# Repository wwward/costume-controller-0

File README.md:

costume-controller-0
====================

Private WIP for ballet costume controller

Using EAGLE 6.5 in "Freemium" mode, FWIW -- wwward

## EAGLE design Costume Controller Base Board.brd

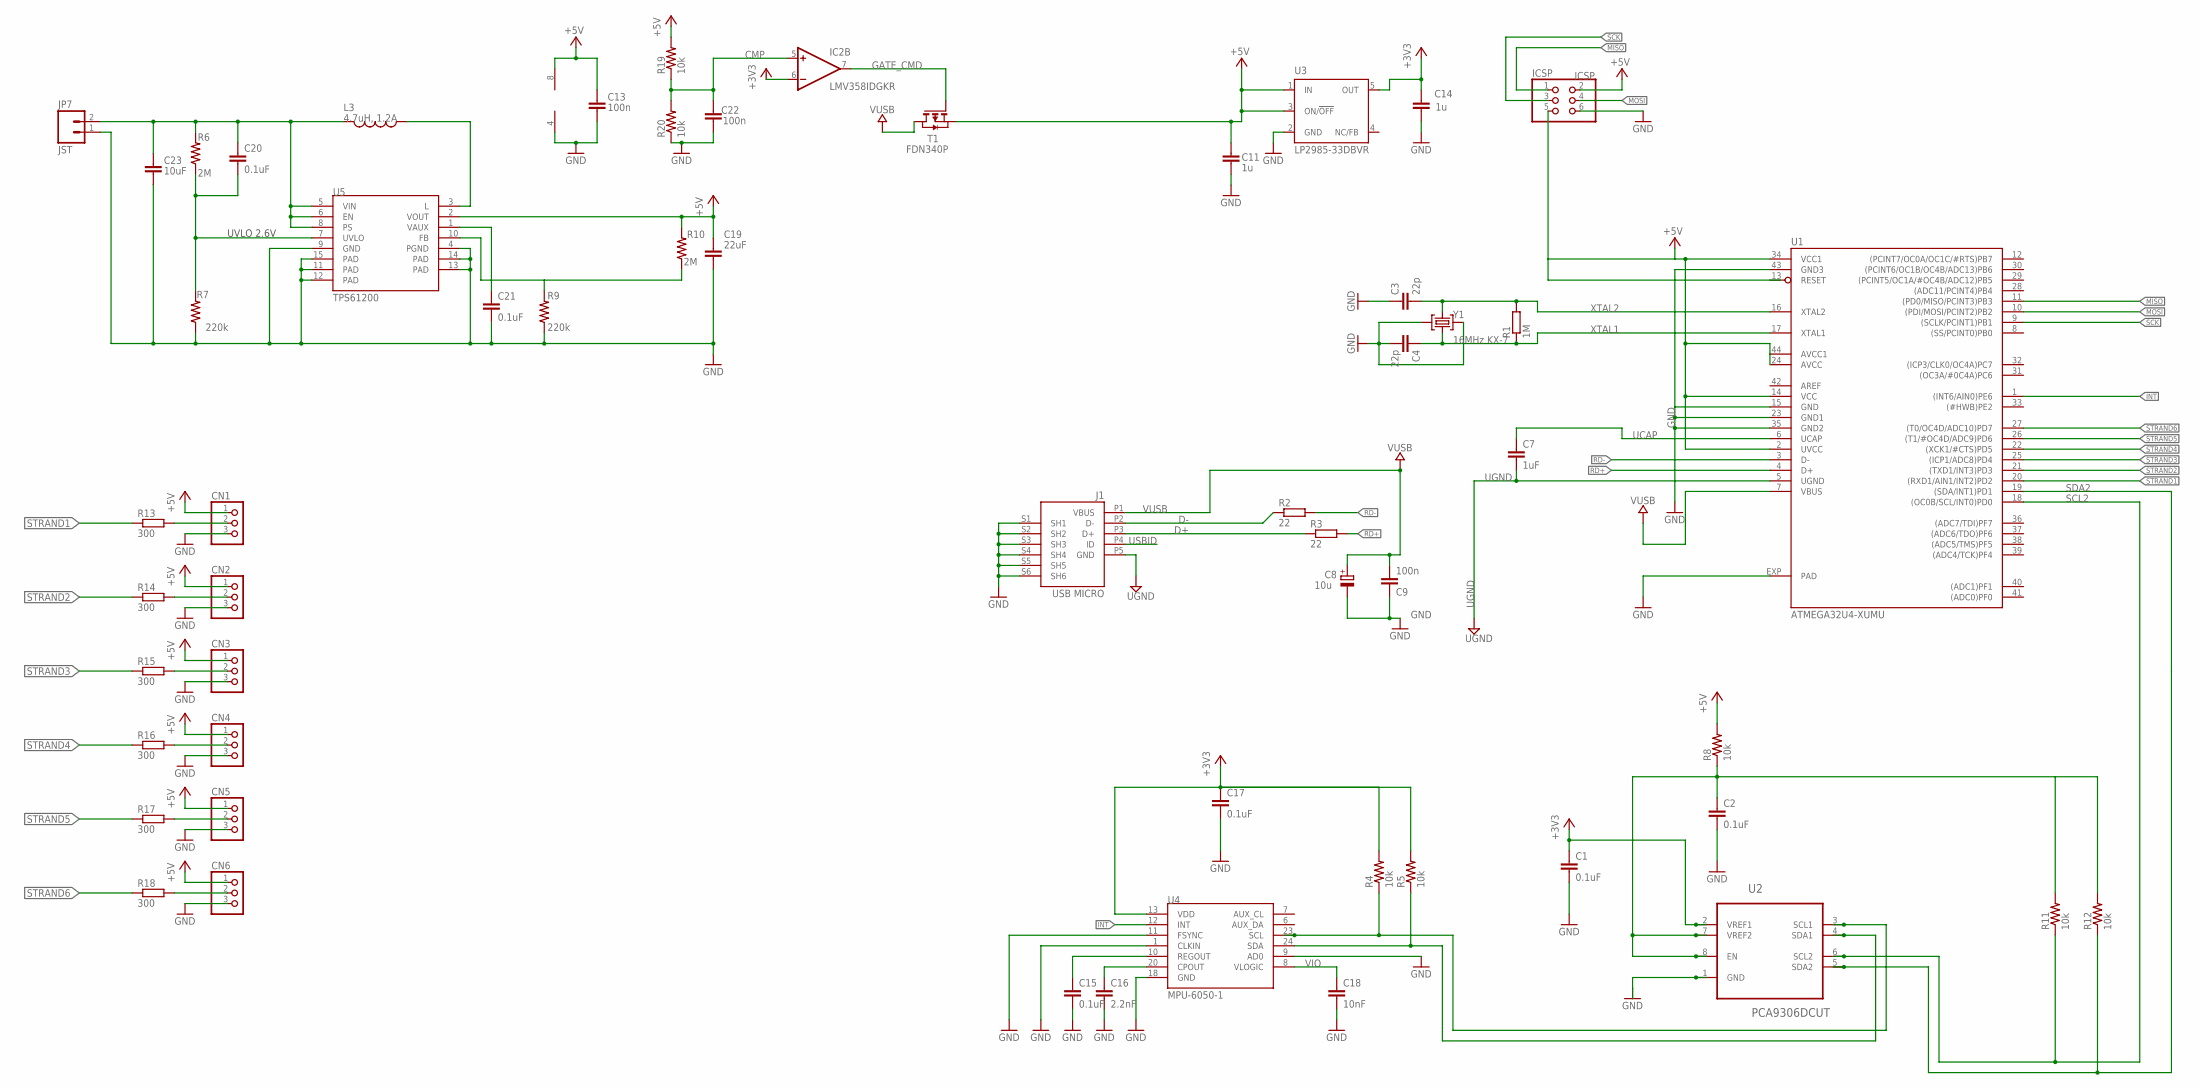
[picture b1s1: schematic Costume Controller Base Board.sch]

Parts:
C1, C2, C15, C17, C20, C21: 0.1uF; 0603-CAP
C3, C4: 22p; C0603-ROUND
C7: 1uF; C0603-ROUND
C8: 10u; SMC_B
C9, C13, C22: 100n; C0603-ROUND
C11, C14: 1u; C0603-ROUND
C16: 2.2nF; 0603-CAP
C18: 10nF; 0603-CAP
C19: 22uF; C0603
C23: 10uF; 1206
CN1, CN2, CN3, CN4, CN5, CN6: JST_3PIN; JSTPH3
IC2: LMV358IDGKR; MSOP08
ICSP: ICSP; 2X03
J1: USB MICRO; CON2_USB_MICRO_B_AT
JP7: JST; JST-2-SMD
L3: 4.7uH, 1.2A; CDRH2D09
R1: 1M; R0603
R2, R3: 22; R0603
R4, R5, R8, R11, R12, R19, R20: 10k; 0603-RES
R6, R10: 2M; 0603-RES
R7, R9: 220k; 0603-RES
R13, R14, R15, R16, R17, R18: 300; R0603
T1: FDN340P; SOT-23
U1: ATMEGA32U4-XUMU; QFN44ML7X7
U2: PCA9306DCUT; SOP50P310X90-8N
U3: LP2985-33DBVR; SOT23-DBV
U4: MPU-6050-1; QFN-24-4MM2
U5: TPS61200; QFN-10_PAD
Y1: 16MHz KX-7; CRYSTAL-3.2-2.5

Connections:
+3V3: C1.1, C14.2, C17.1, IC2.6 (-IN), R4.2, R5.2, U2.2 (VREF1), U3.5 (OUT), U4.13 (VDD)
+5V: C11.2, C13.1, C19.1, CN1.1, CN2.1, CN3.1, CN4.1, CN5.1, CN6.1, IC2.8 (V+), ICSP.2, ICSP.5, R8.2, R10.2, R19.2, T1.2 (S), U1.2 (UVCC), U1.14 (VCC), U1.24 (AVCC), U1.34 (VCC1), U1.44 (AVCC1), U3.1 (IN), U3.3 (ON/!OFF), U5.2 (VOUT)
AREF: U1.42 (AREF)
CMP: C22.2, IC2.5 (+IN), R19.1, R20.2
D+: J1.P3 (D+), R3.1
D-: J1.P2 (D-), R2.1
FB: R9.2, R10.1, U5.10 (FB)
GATE_CMD: IC2.7 (OUT), T1.3 (G)
GND: C1.2, C2.2, C3.1, C4.2, C8.-, C9.1, C11.1, C13.2, C14.1, C15.2, C16.2, C17.2, C18.2, C19.2, C21.2, C22.1, C23.2, CN1.3, CN2.3, CN3.3, CN4.3, CN5.3, CN6.3, IC2.4 (V-), ICSP.6, J1.S1 (SH1), J1.S2 (SH2), J1.S3 (SH3), J1.S4 (SH4), J1.S5 (SH5), J1.S6 (SH6), JP7.1, R7.1, R9.1, R20.1, U1.15 (GND), U1.23 (GND1), U1.35 (GND2), U1.43 (GND3), U1.EXP (PAD), U2.1 (GND), U3.2 (GND), U4.1 (CLKIN), U4.9 (AD0), U4.11 (FSYNC), U4.18 (GND), U5.4 (PGND), U5.9 (GND), U5.11 (PAD), U5.12 (PAD), U5.13 (PAD), U5.14 (PAD), U5.15 (PAD), Y1.2 (GND), Y1.4 (GND)
INT: U1.1 ((INT6/AIN0)PE6), U4.12 (INT)
MISO: ICSP.1, U1.11 ((PD0/MISO/PCINT3)PB3)
MOSI: ICSP.4, U1.10 ((PDI/MOSI/PCINT2)PB2)
unnamed: C16.1, U4.20 (CPOUT)
unnamed: C2.1, R8.1, R11.2, R12.2, U2.7 (VREF2), U2.8 (EN)
unnamed: CN6.2, R18.2
unnamed: L3.P$1 (1), U5.3 (L)
unnamed: C15.1, U4.10 (REGOUT)
unnamed: CN5.2, R17.2
unnamed: CN4.2, R16.2
unnamed: CN3.2, R15.2
unnamed: C21.1, U5.1 (VAUX)
unnamed: CN2.2, R14.2
unnamed: CN1.2, R13.2
RD+: R3.2, U1.4 (D+)
RD-: R2.2, U1.3 (D-)
SCK: ICSP.3, U1.9 ((SCLK/PCINT1)PB1)
SCL1: R4.1, U2.3 (SCL1), U4.23 (SCL)
SCL2: R11.1, U1.18 ((OC0B/SCL/INT0)PD0), U2.6 (SCL2)
SDA1: R5.1, U2.4 (SDA1), U4.24 (SDA)
SDA2: R12.1, U1.19 ((SDA/INT1)PD1), U2.5 (SDA2)
STRAND1: R13.1, U1.20 ((RXD1/AIN1/INT2)PD2)
STRAND2: R14.1, U1.21 ((TXD1/INT3)PD3)
STRAND3: R15.1, U1.25 ((ICP1/ADC8)PD4)
STRAND4: R16.1, U1.22 ((XCK1/#CTS)PD5)
STRAND5: R17.1, U1.26 ((T1/#OC4D/ADC9)PD6)
STRAND6: R18.1, U1.27 ((T0/OC4D/ADC10)PD7)
UCAP: C7.1, U1.6 (UCAP)
UGND: C7.2, J1.P5 (GND), U1.5 (UGND)
USBID: J1.P4 (ID)
UVLO: C20.2, R6.1, R7.2, U5.7 (UVLO)
VIN: C20.1, C23.1, JP7.2, L3.P$2 (2), R6.2, U5.5 (VIN), U5.6 (EN), U5.8 (PS)
VIO: C18.1, U4.8 (VLOGIC)
VUSB: C8.+, C9.2, J1.P1 (VBUS), T1.1 (D), U1.7 (VBUS)
XTAL1: C4.1, R1.1, U1.17 (XTAL1), Y1.1 (C1)
XTAL2: C3.2, R1.2, U1.16 (XTAL2), Y1.3 (C2)

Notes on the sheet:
UVLO 2.6V

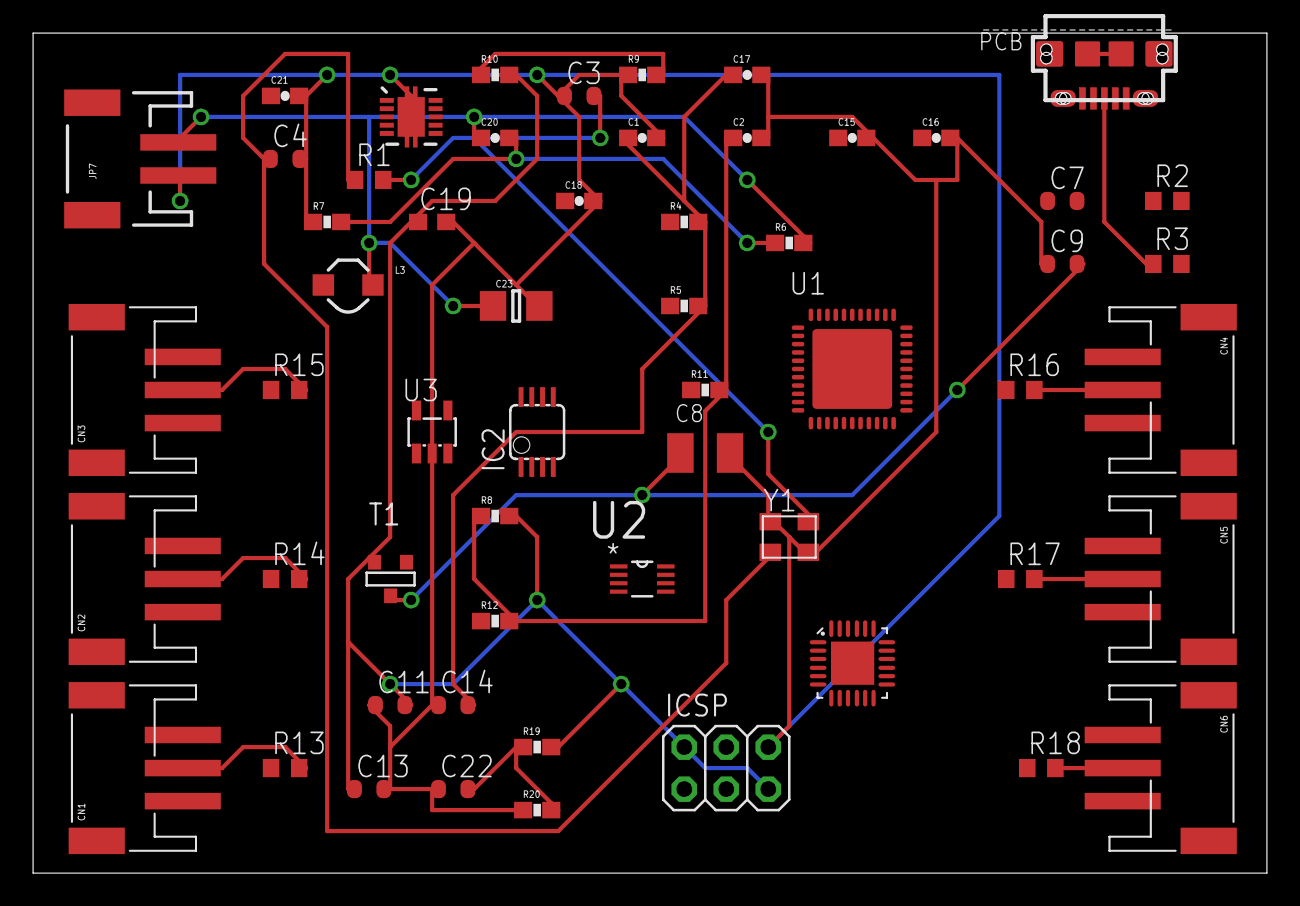
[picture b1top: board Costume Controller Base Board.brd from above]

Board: 2 copper layers, 74.6 x 50.8 mm, 57 parts (0 on the bottom side), 43 nets.

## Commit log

2014-03-06 Initial
2014-03-09 Added 3.3v regulator
2014-03-09 Some joining of grounds and such, need to review nets and busses, eliminated stray resistors, will replace resistor nets with discrete resistors -- www
2014-03-10 modified nets, removed extraneous components
2014-03-11 added TI level translator
2014-03-11 complete schematic, though VUSB needs further study, probably won't power +5v
2014-03-11 removed autocreated schematic backups
2014-03-12 added pullups
2014-03-16 Draft, proofreading required, some components need package changes or value confirmation, board layout and routing required.
